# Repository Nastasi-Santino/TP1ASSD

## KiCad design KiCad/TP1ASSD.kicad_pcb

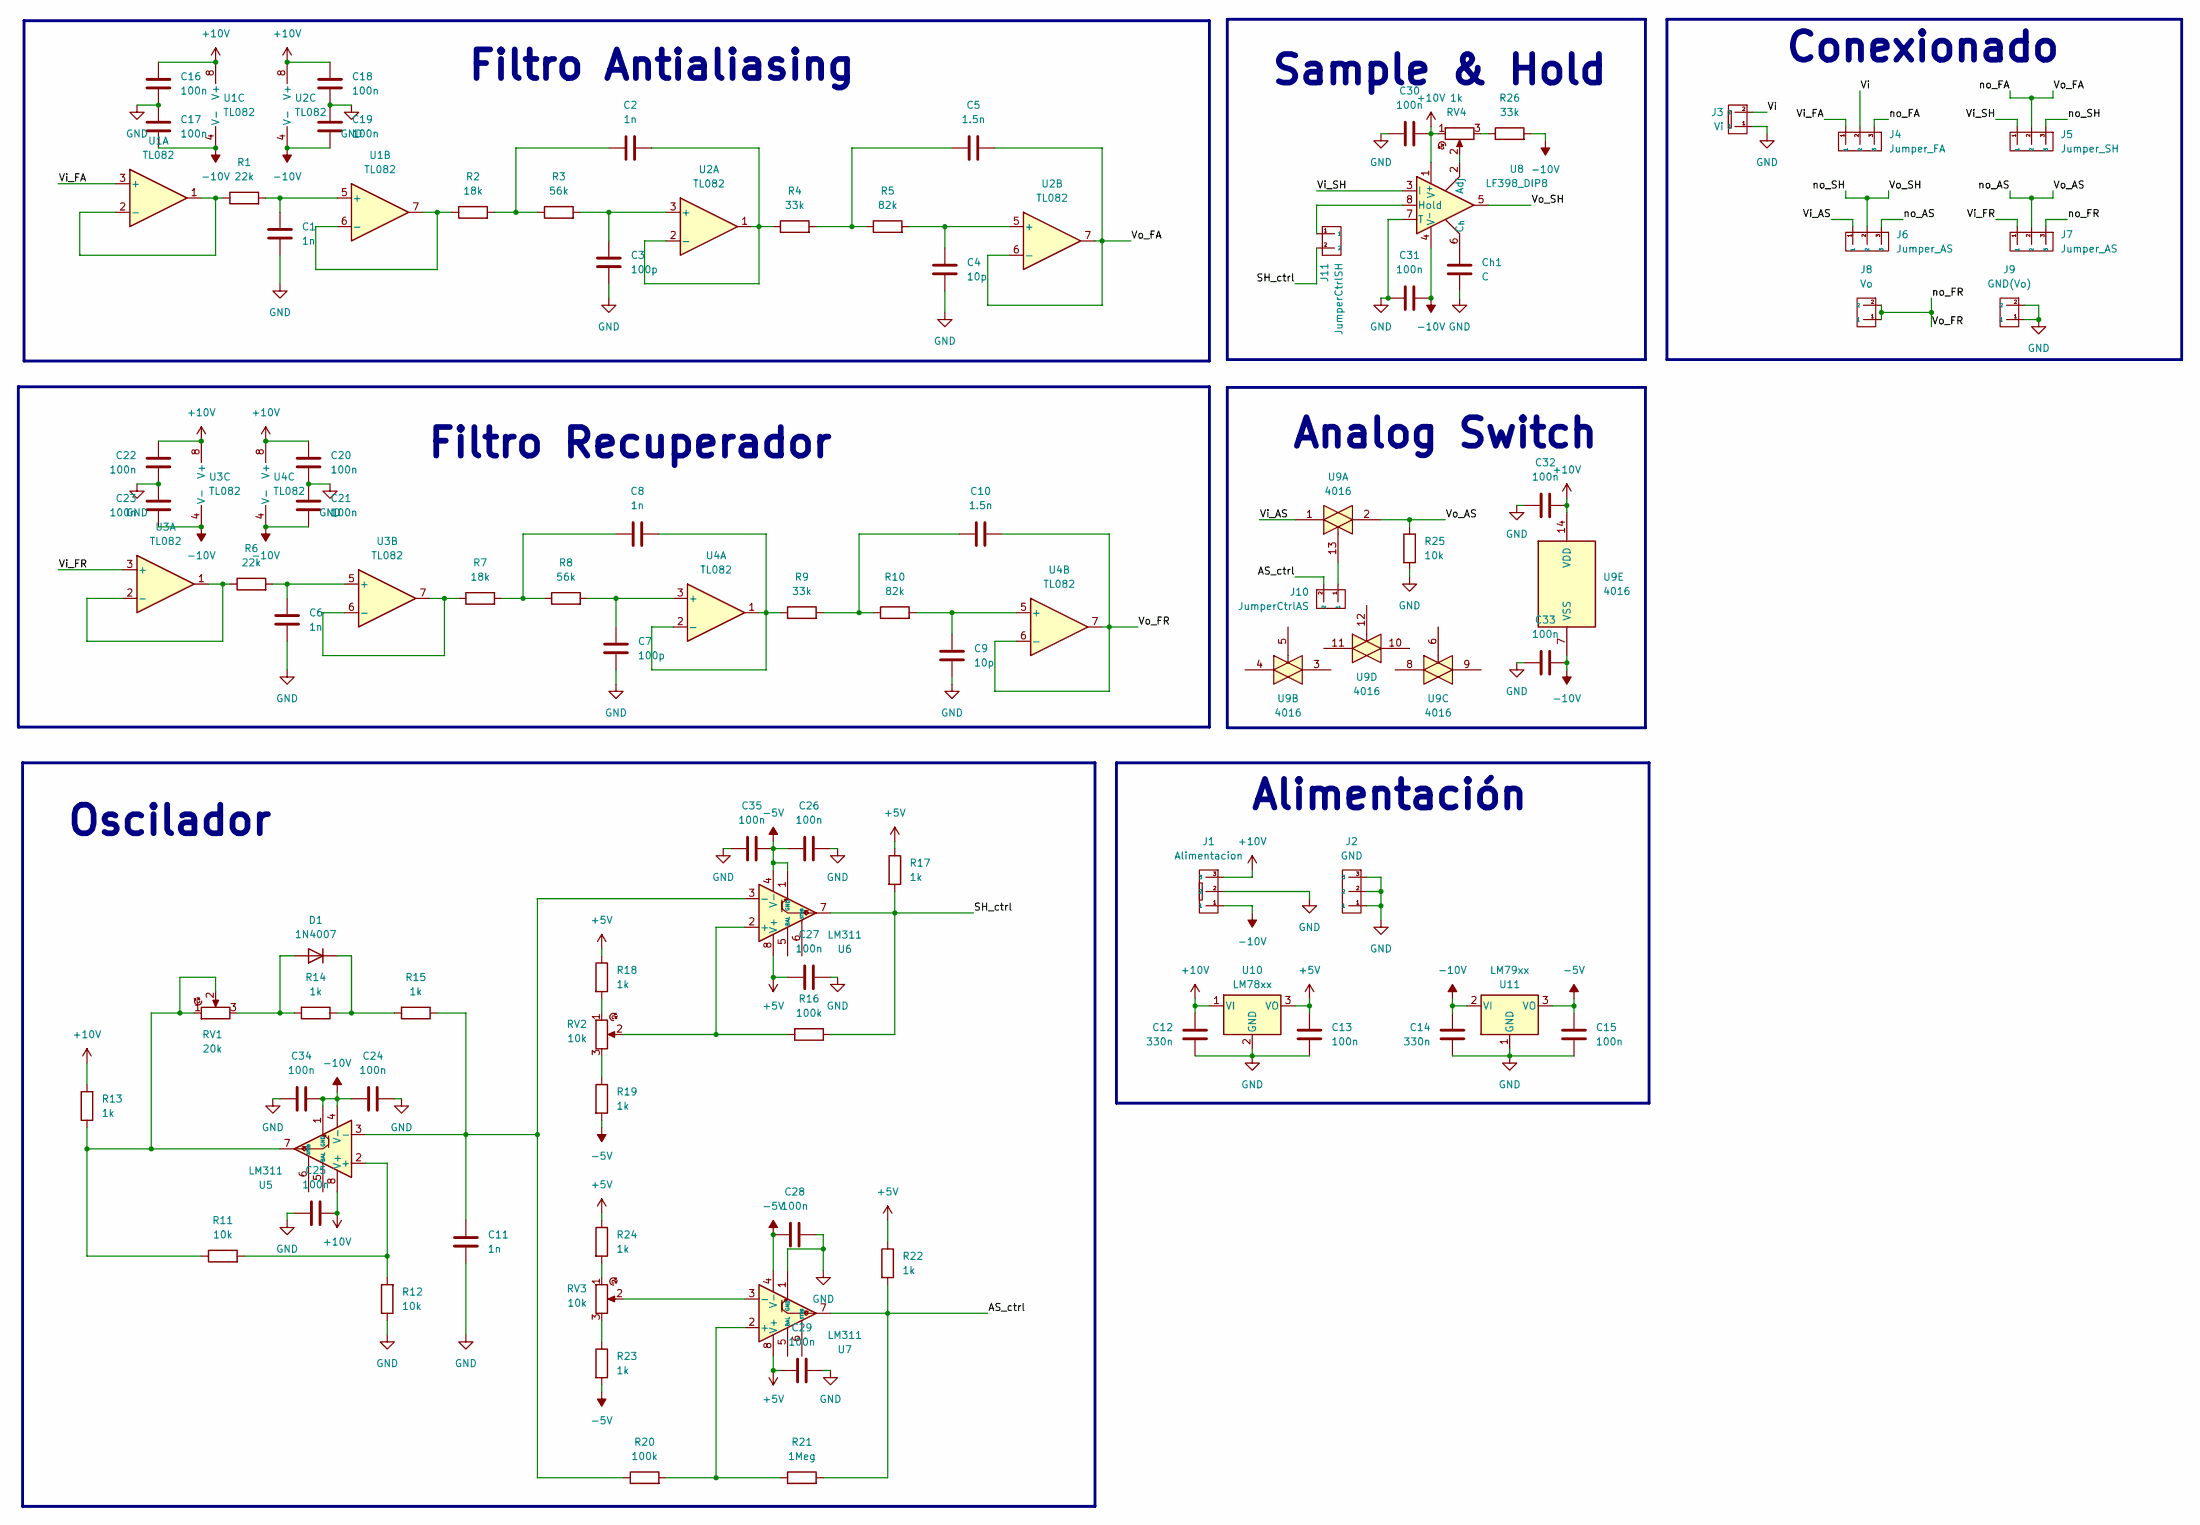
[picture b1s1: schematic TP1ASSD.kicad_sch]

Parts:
C1, C2, C6, C8, C11: 1n; C_0805
C3, C7: 100p; C_0805
C4, C9: 10p; C_0805
C5, C10: 1.5n; C_0805
C12, C14: 330n; C_0805
C13, C15, C35: 100n; C_0805
C16, C17, C18, C19, C20, C21, C22, C23, C24, C25, C26, C27, C28, C29, C30, C31, C33, C34: 100n; C_5mm
C32: 100n; C_2.5mm
Ch1: C; C_5mm
D1: 1N4007; D_DO-41
J1: Alimentacion; Molex_1x03_P2.54mm
J2: GND; PinHeader_1x03_P2.54mm_Vertical
J3: Vi; Molex_1x02_P2.54mm
J4: Jumper_FA; PinHeader_1x03_P2.54mm_Vertical
J5: Jumper_SH; PinHeader_1x03_P2.54mm_Vertical
J6, J7: Jumper_AS; PinHeader_1x03_P2.54mm_Vertical
J8: Vo; PinHeader_1x02_P2.54mm_Vertical
J9: GND(Vo); PinHeader_1x02_P2.54mm_Vertical
J10: JumperCtrlAS; PinHeader_1x02_P2.54mm_Vertical
J11: JumperCtrlSH; PinHeader_1x02_P2.54mm_Vertical
R1, R6: 22k; R_0.25W
R2, R7: 18k; R_0805
R3, R8: 56k; R_0805
R4, R9: 33k; R_0805
R5, R10: 82k; R_0.25W
R11, R12: 10k; R_0805
R13, R14, R15, R17, R18, R19, R22, R23, R24: 1k; R_0805
R16, R20: 100k; R_0.25W
R21: 1Meg; R_0.25W
R25: 10k; R_0.25W
R26: 33k; R_0.25W
RV1: 20k; RV_Preset_multivuelta_10mm_5mm
RV2, RV3: 10k; RV_Preset_multivuelta_10mm_5mm
RV4: 1k; RV_Preset_multivuelta_10mm_5mm
U1, U2, U3, U4: TL082; DIP-8_W7.62mm
U5, U6, U7: LM311; DIP-8_W7.62mm
U8: LF398_DIP8; DIP-8_W7.62mm
U9: 4016; DIP-14_W7.62mm
U10: LM78xx; TO-220-3_Vertical
U11: LM79xx; TO-220-3_Vertical

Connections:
+5V: C13.1, C27.1, C29.1, R17.1, R18.1, R22.1, R24.1, U6.8 (V+), U7.8 (V+), U10.3 (VO)
+10V: C12.1, C16.1, C18.1, C20.1, C22.1, C25.2, C30.1, C32.1, J1.3, R13.2, RV4.1, U1.8 (V+), U2.8 (V+), U3.8 (V+), U4.8 (V+), U5.8 (V+), U8.1 (V^{+}), U9.14 (VDD), U10.1 (VI)
-5V: C15.1, C26.1, C28.1, C35.1, R19.2, R23.2, U6.1 (GND), U6.4 (V-), U7.4 (V-), U11.3 (VO)
-10V: C14.1, C17.2, C19.2, C21.2, C23.2, C24.1, C31.1, C33.1, C34.1, J1.1, R26.2, U1.4 (V-), U2.4 (V-), U3.4 (V-), U4.4 (V-), U5.1 (GND), U5.4 (V-), U8.4 (V^{-}), U9.7 (VSS), U11.2 (VI)
/AS_ctrl: J10.2, R21.2, R22.2, U7.7
/SH_ctrl: J11.2, R16.1, R17.2, U6.7
/Vi: J3.2, J4.2
/Vi_AS: J6.1, U9.1
/Vi_FA: J4.1, U1.3 (+)
/Vi_FR: J7.1, U3.3 (+)
/Vi_SH: J5.1, U8.3 (I)
/Vo_AS: J6.3, J7.2, R25.1, U9.2
/Vo_FA: C5.2, J4.3, J5.2, U2.6 (-), U2.7
/Vo_FR: C10.2, J7.3, J8.1, J8.2, U4.6 (-), U4.7
/Vo_SH: J5.3, J6.2, U8.5
GND: C1.2, C3.2, C4.2, C6.2, C7.2, C9.2, C11.2, C12.2, C13.2, C14.2, C15.2, C16.2, C17.1, C18.2, C19.1, C20.2, C21.1, C22.2, C23.1, C24.2, C25.1, C26.2, C27.2, C28.2, C29.2, C30.2, C31.2, C32.2, C33.2, C34.2, C35.2, Ch1.2, J1.2, J2.1, J2.2, J2.3, J3.1, J9.1, J9.2, R12.1, R25.2, U7.1 (GND), U8.7 (T), U10.2 (GND), U11.1 (GND)
unnamed: C2.1, R2.2, R3.1
unnamed: C5.1, R4.2, R5.1
unnamed: C8.1, R7.2, R8.1
unnamed: C10.1, R9.2, R10.1
unnamed: D1.2 (A), R14.2, RV1.3
unnamed: D1.1 (K), R14.1, R15.2
unnamed: J10.1, U9.13
unnamed: R11.1, R13.1, RV1.1, RV1.2, U5.7
unnamed: R18.2, RV2.1
unnamed: R19.1, RV2.3
unnamed: R23.1, RV3.3
unnamed: R24.2, RV3.1
unnamed: R26.1, RV4.3
unnamed: R1.1, U1.1, U1.2 (-)
unnamed: C1.1, R1.2, U1.5 (+)
unnamed: R2.1, U1.6 (-), U1.7
unnamed: C3.1, R3.2, U2.3 (+)
unnamed: C2.2, R4.1, U2.1, U2.2 (-)
unnamed: C4.1, R5.2, U2.5 (+)
unnamed: R6.1, U3.1, U3.2 (-)
unnamed: C6.1, R6.2, U3.5 (+)
unnamed: R7.1, U3.6 (-), U3.7
unnamed: C7.1, R8.2, U4.3 (+)
unnamed: C8.2, R9.1, U4.1, U4.2 (-)
unnamed: C9.1, R10.2, U4.5 (+)
unnamed: R11.2, R12.2, U5.2 (+)
unnamed: C11.1, R15.1, R20.1, U5.3 (-), U6.3 (-)
unnamed: R16.2, RV2.2, U6.2 (+)
unnamed: R20.2, R21.1, U7.2 (+)
unnamed: RV3.2, U7.3 (-)
unnamed: RV4.2, U8.2 (Adj)
unnamed: Ch1.1, U8.6 (C_{h})
unnamed: J11.1, U8.8 (Hold)

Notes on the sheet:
Filtro Recuperador
Filtro Antialiasing
Sample & Hold
Conexionado
Analog Switch
Alimentación
Oscilador

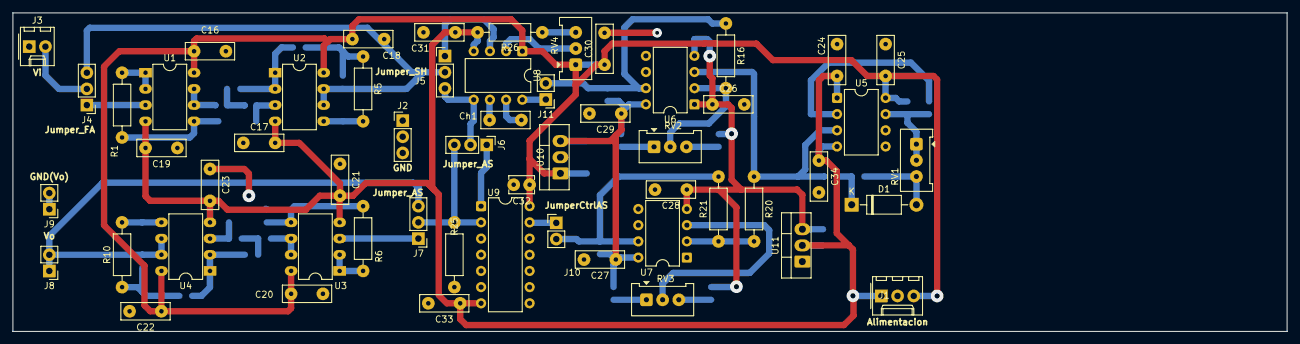
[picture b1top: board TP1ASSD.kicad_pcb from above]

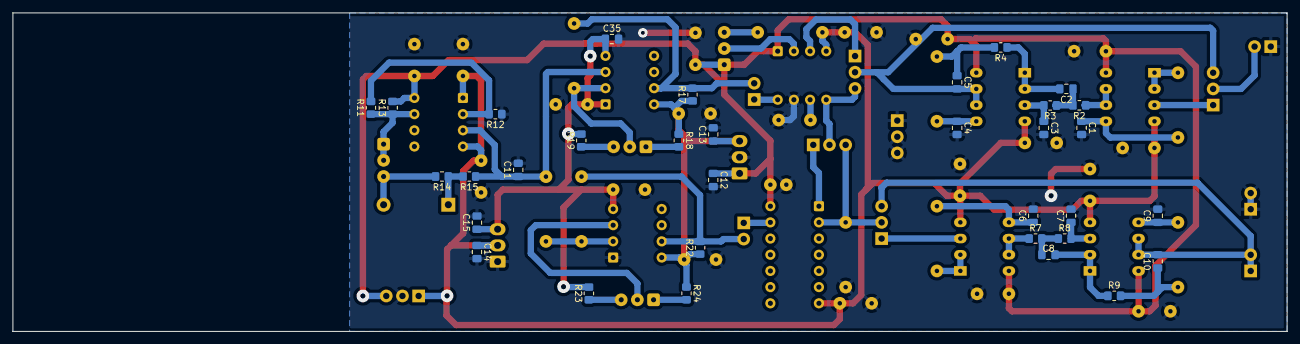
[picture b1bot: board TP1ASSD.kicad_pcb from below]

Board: 2 copper layers, 200.0 x 50.0 mm, 89 parts (33 on the bottom side), 49 nets.

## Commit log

2026-03-20 Agrego Kicad
2026-03-20 ruteo del Sample and hold y de la llave
2026-03-21 Acomode la bottom y agregue el plano de masa abajo. Creo que ya esta ruteado todo lo signal-related.
2026-03-21 Acomode la bottom y creo que ya ruteado todo lo signal-related
2026-03-21 Agregue capas de desacople y DC zerooing para el SH
2026-03-22 Empece a rutear la alimentacion
2026-03-22 Termine alimentacion
2026-03-24 Front silkscreen text size increased
2026-03-24 Visualization on top of front silkscreen layer
